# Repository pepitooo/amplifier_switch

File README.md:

View this project on [CADLAB.io](https://cadlab.io/project/1182). 

# amplifier_switch

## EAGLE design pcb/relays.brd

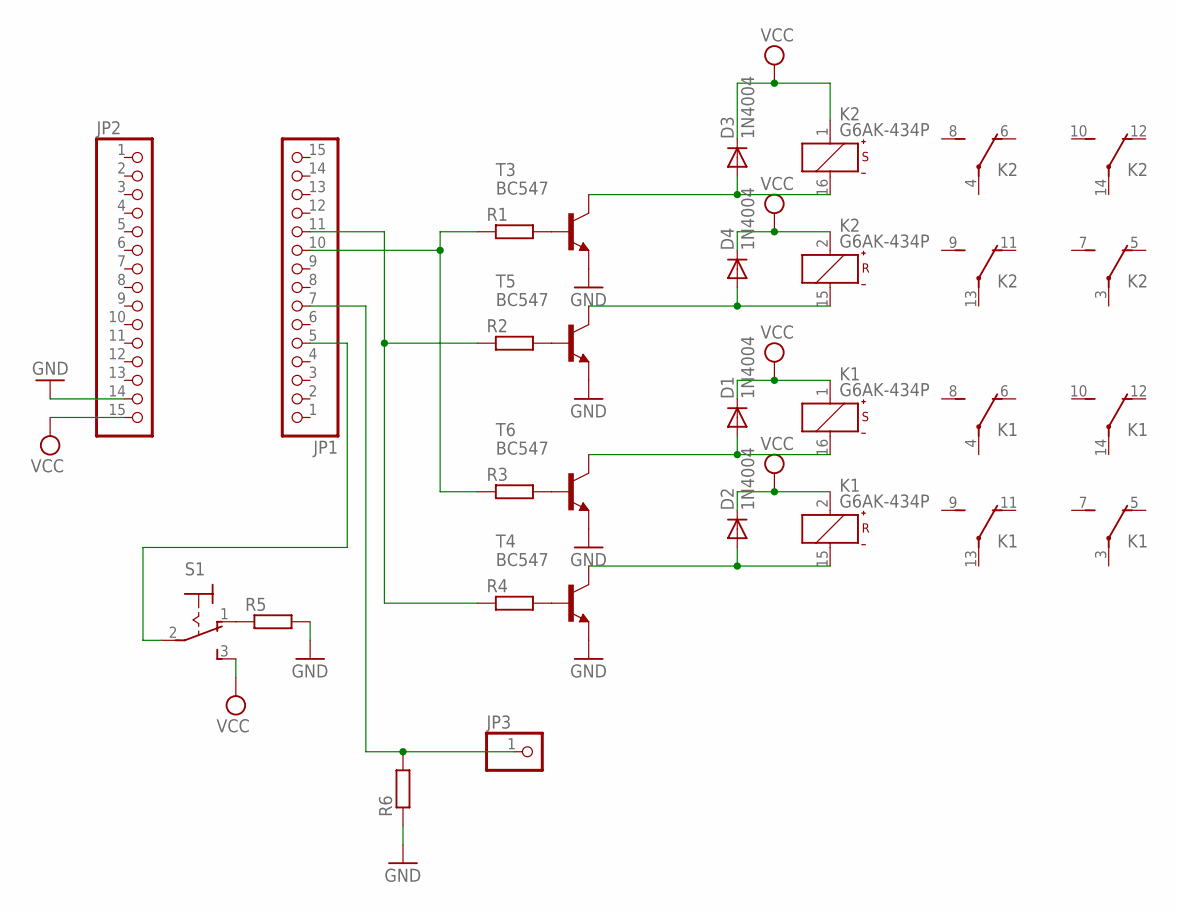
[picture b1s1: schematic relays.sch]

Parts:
D1, D2, D3, D4: 1N4004; DO41-10
JP1, JP2: PINHD-1X15; 1X15
JP3: PINHD-1X1; 1X01
K1, K2: G6AK-434P
R1, R2, R3, R4, R5, R6: R-EU_0207/10; 0207/10
S1: 320-916
T3, T4, T5, T6: BC547; TO92

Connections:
GND: JP2.14, R5.2, R6.1, T3.1 (E), T4.1 (E), T5.1 (E), T6.1 (E)
unnamed: R1.2, T3.2 (B)
unnamed: D3.A, K2.16 (-), T3.3 (C)
unnamed: R2.2, T5.2 (B)
unnamed: D4.A, K2.15 (-), T5.3 (C)
unnamed: D1.A, K1.16 (-), T6.3 (C)
unnamed: R3.2, T6.2 (B)
unnamed: R4.2, T4.2 (B)
unnamed: D2.A, K1.15 (-), T4.3 (C)
unnamed: R5.1, S1.1 (O)
unnamed: JP1.5, S1.2
unnamed: JP1.11, R2.1, R4.1
unnamed: JP1.10, R1.1, R3.1
unnamed: JP1.7, JP3.1, R6.2
VCC: D1.C, D2.C, D3.C, D4.C, JP2.15, K1.1 (+), K1.2 (+), K2.1 (+), K2.2 (+), S1.3 (S)

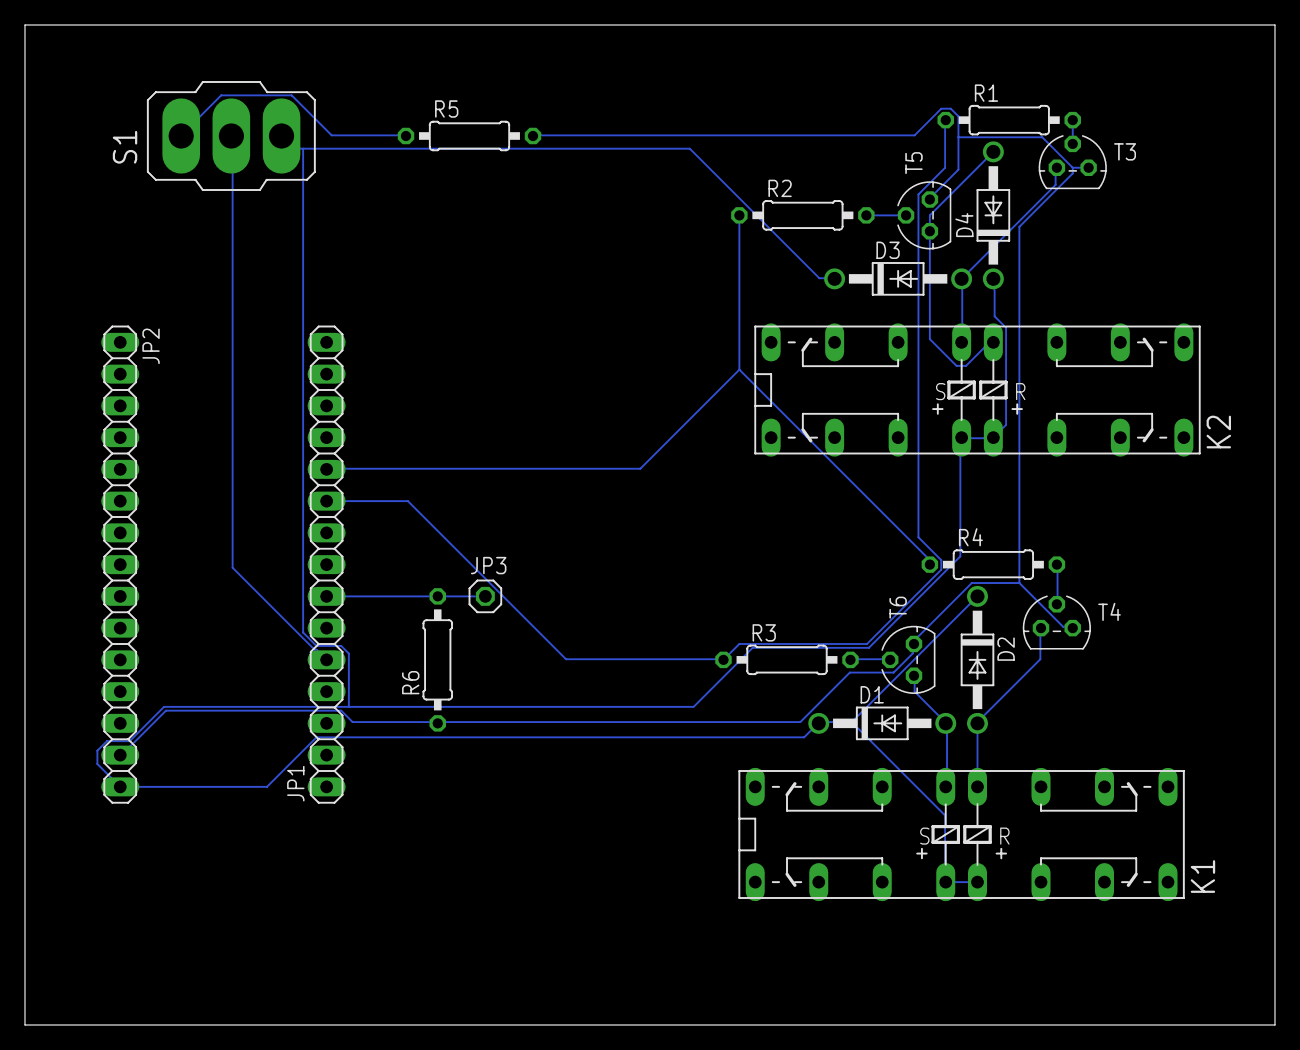
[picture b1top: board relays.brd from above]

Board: 2 copper layers, 100.0 x 80.0 mm, 20 parts (0 on the bottom side), 15 nets.

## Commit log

2018-06-20 Backlink to CADLAB.io has been added.
2018-06-22 insert schematic
